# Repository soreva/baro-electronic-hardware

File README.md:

# README #

### What is this repository for? ###

This repository hosts the engineering designs for the Electronic Barometer designed by Soreva for use by SGS Weather and Environmental Systems.

### Who do I talk to? ###

Anirudh Ramesh, anirudh@soreva.co.in

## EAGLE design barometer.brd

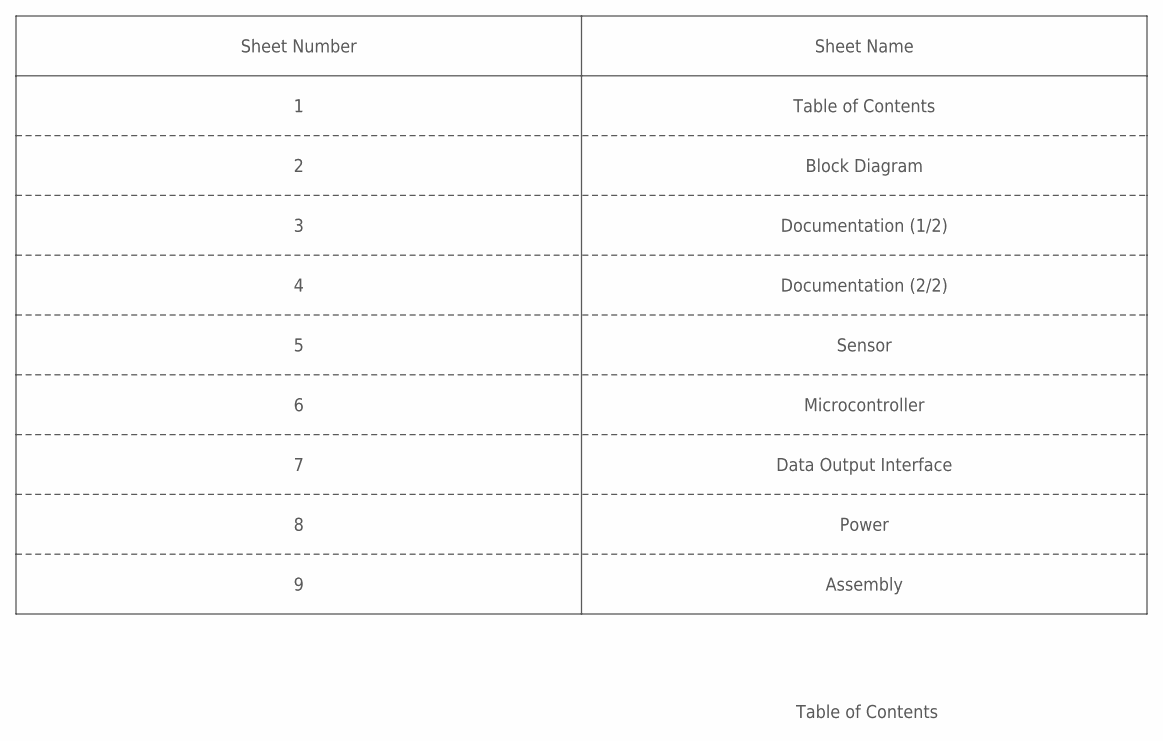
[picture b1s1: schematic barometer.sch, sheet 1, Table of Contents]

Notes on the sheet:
Table of Contents
Sheet Number
Sheet Name
Block Diagram
Documentation (1/2)
Documentation (2/2)
Sensor
Microcontroller
Data Output Interface
Power
Assembly

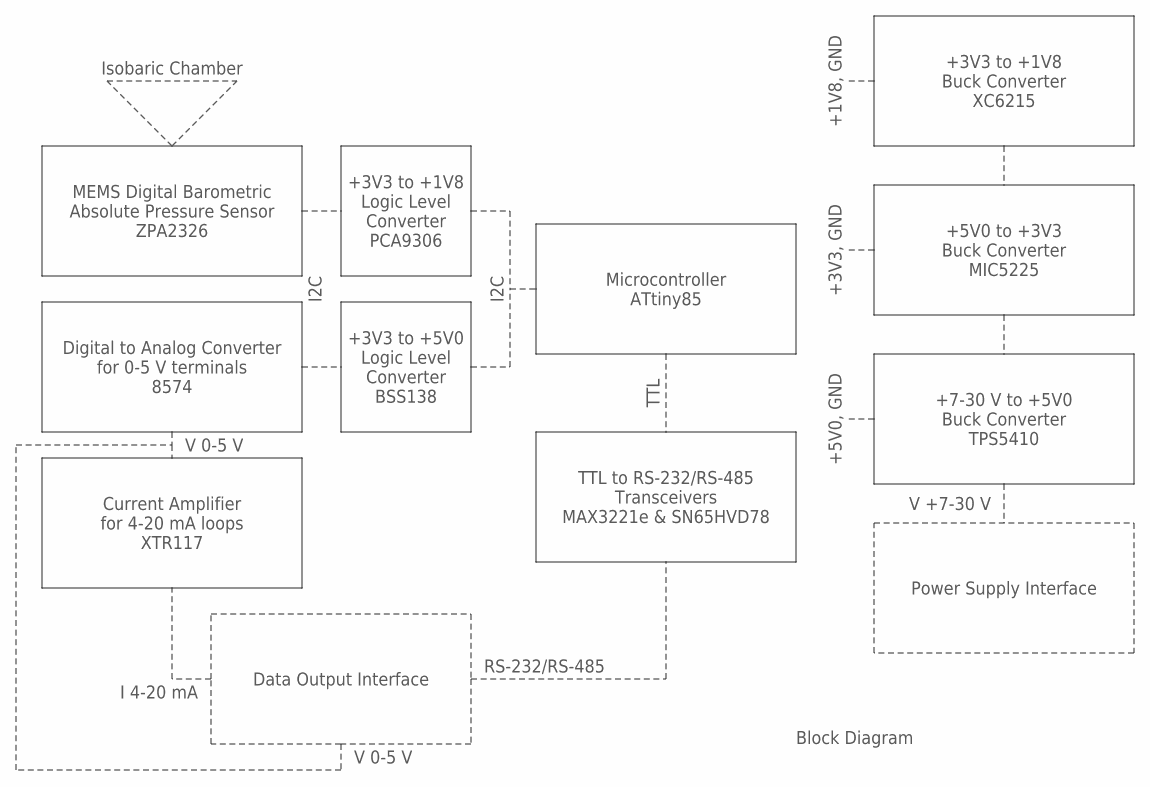
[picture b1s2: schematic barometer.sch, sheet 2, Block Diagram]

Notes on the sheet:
Block Diagram
MEMS Digital Barometric Absolute Pressure Sensor ZPA2326
Microcontroller ATtiny85
Digital to Analog Converter for 0-5 V terminals 8574
TTL to RS-232/RS-485 Transceivers MAX3221e & SN65HVD78
TTL
I2C
+3V3 to +1V8 Logic Level Converter PCA9306
+3V3 to +5V0 Logic Level Converter BSS138
Current Amplifier for 4-20 mA loops XTR117
Isobaric Chamber
Data Output Interface
Power Supply Interface
+7-30 V to +5V0 Buck Converter TPS5410
+5V0 to +3V3 Buck Converter MIC5225
+3V3 to +1V8 Buck Converter XC6215
V 0-5 V
I 4-20 mA
RS-232/RS-485
+5V0, GND
+3V3, GND
+1V8, GND
V +7-30 V

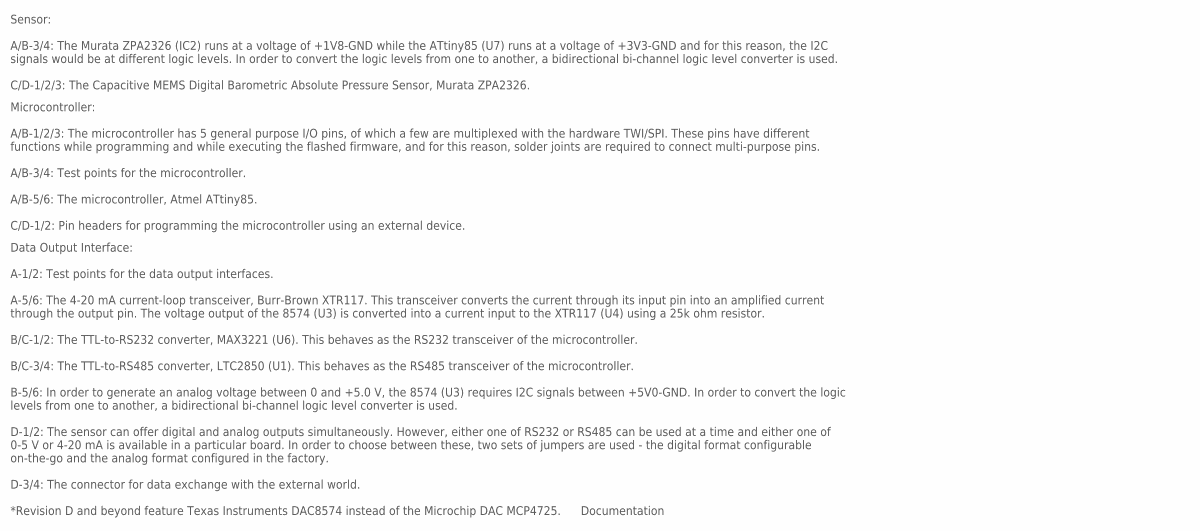
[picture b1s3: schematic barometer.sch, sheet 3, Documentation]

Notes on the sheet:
Documentation
Sensor: A/B-3/4: The Murata ZPA2326 (IC2) runs at a voltage of +1V8-GND while the ATtiny85 (U7) runs at a voltage of +3V3-GND and for this reason, the I2C signals would be at different logic levels. In order to convert the logic levels from one to another, a bidirectional bi-channel logic level con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
Microcontroller: A/B-1/2/3: The microcontroller has 5 general purpose I/O pins, of which a few are multiplexed with the hardware TWI/SPI. These pins have different functions while programming and while executing the flashed firmware, and for this reason, solder joints are required to connect multi-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
Data Output Interface: A-1/2: Test points for the data output interfaces. A-5/6: The 4-20 mA current-loop transceiver, Burr-Brown XTR117. This transceiver converts the current through its input pin into an amplified current through the output pin. The voltage output of the 8574 (U3) is converted in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

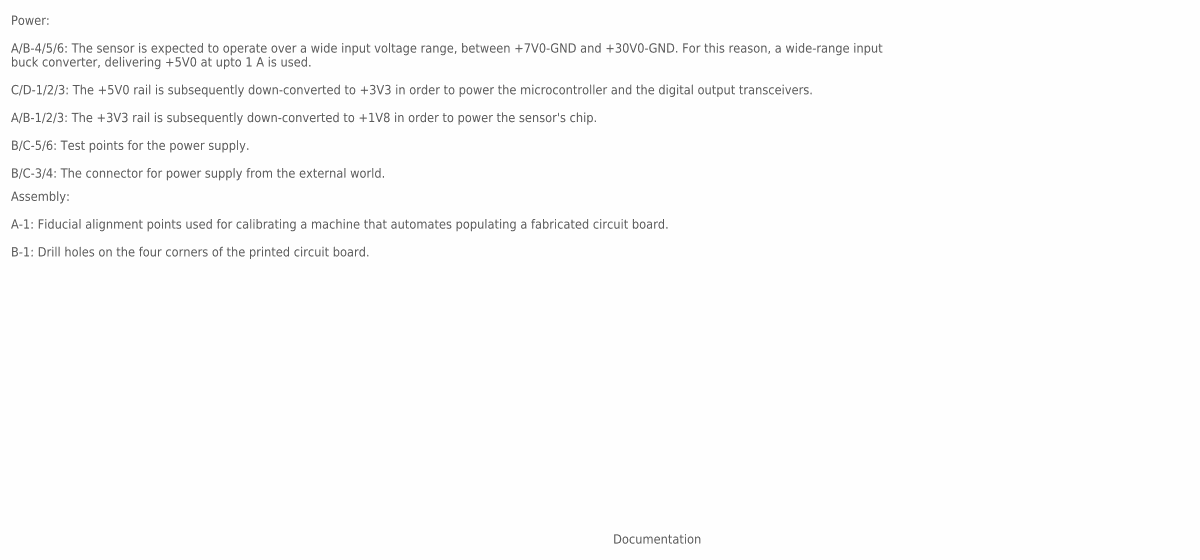
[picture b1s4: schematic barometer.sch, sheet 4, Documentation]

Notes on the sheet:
Documentation
Power: A/B-4/5/6: The sensor is expected to operate over a wide input voltage range, between +7V0-GND and +30V0-GND. For this reason, a wide-range input buck converter, delivering +5V0 at upto 1 A is used. C/D-1/2/3: The +5V0 rail is subsequently down-converted to +3V3 in order to power the microco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
Assembly: A-1: Fiducial alignment points used for calibrating a machine that automates populating a fabricated circuit board. B-1: Drill holes on the four corners of the printed circuit board.

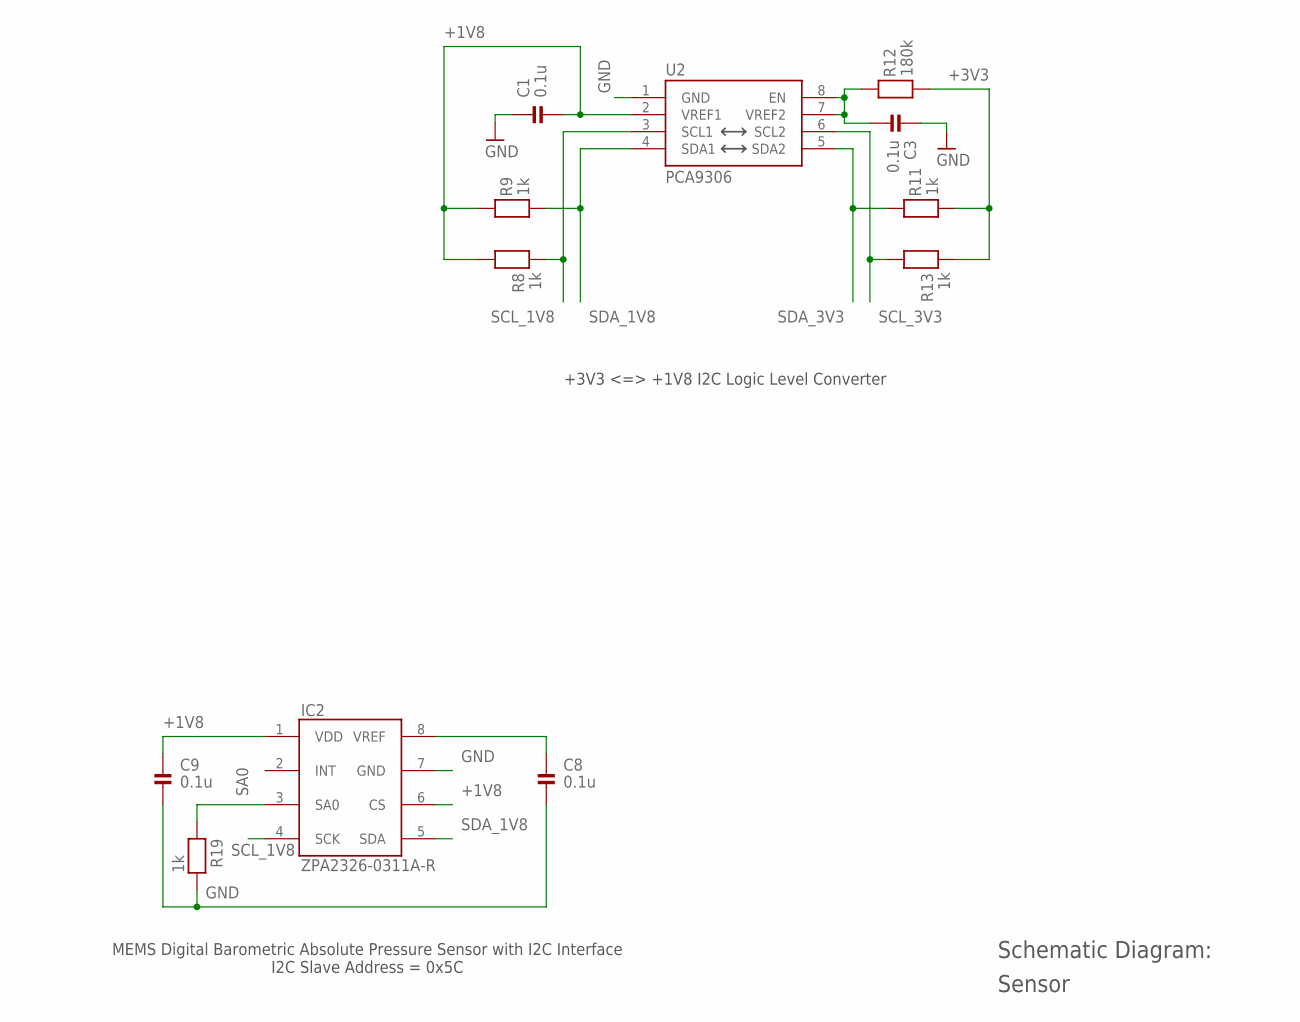
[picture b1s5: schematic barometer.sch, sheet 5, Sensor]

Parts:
C1, C3, C8, C9: 0.1u; 0603
IC2: ZPA2326-0311A-R; 2326
R8, R9, R11, R13, R19: 1k; 0603
R12: 180k; 0603
U2: PCA9306; PSOP-8

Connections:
+1V8: C1.2, C9.1, IC2.1 (VDD), IC2.6 (CS), R8.2, R9.2, U2.2 (VREF1); also elsewhere on the board
+3V3: R11.1, R12.1, R13.1; also elsewhere on the board
GND: C1.1, C3.1, C8.2, C9.2, IC2.7 (GND), R19.2, U2.1 (GND); also elsewhere on the board
SA0: IC2.3 (SA0), R19.1
SCL_1V8: IC2.4 (SCK), R8.1, U2.3 (SCL1)
SCL_3V3: R13.2, U2.6 (SCL2); also elsewhere on the board
SDA_1V8: IC2.5 (SDA), R9.1, U2.4 (SDA1)
SDA_3V3: R11.2, U2.5 (SDA2); also elsewhere on the board
VREF: C8.1, IC2.8 (VREF)
VREF_3V3: C3.2, R12.2, U2.7 (VREF2), U2.8 (EN)

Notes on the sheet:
Sensor
MEMS Digital Barometric Absolute Pressure Sensor with I2C Interface I2C Slave Address = 0x5C
+3V3 <=> +1V8 I2C Logic Level Converter
Schematic Diagram:

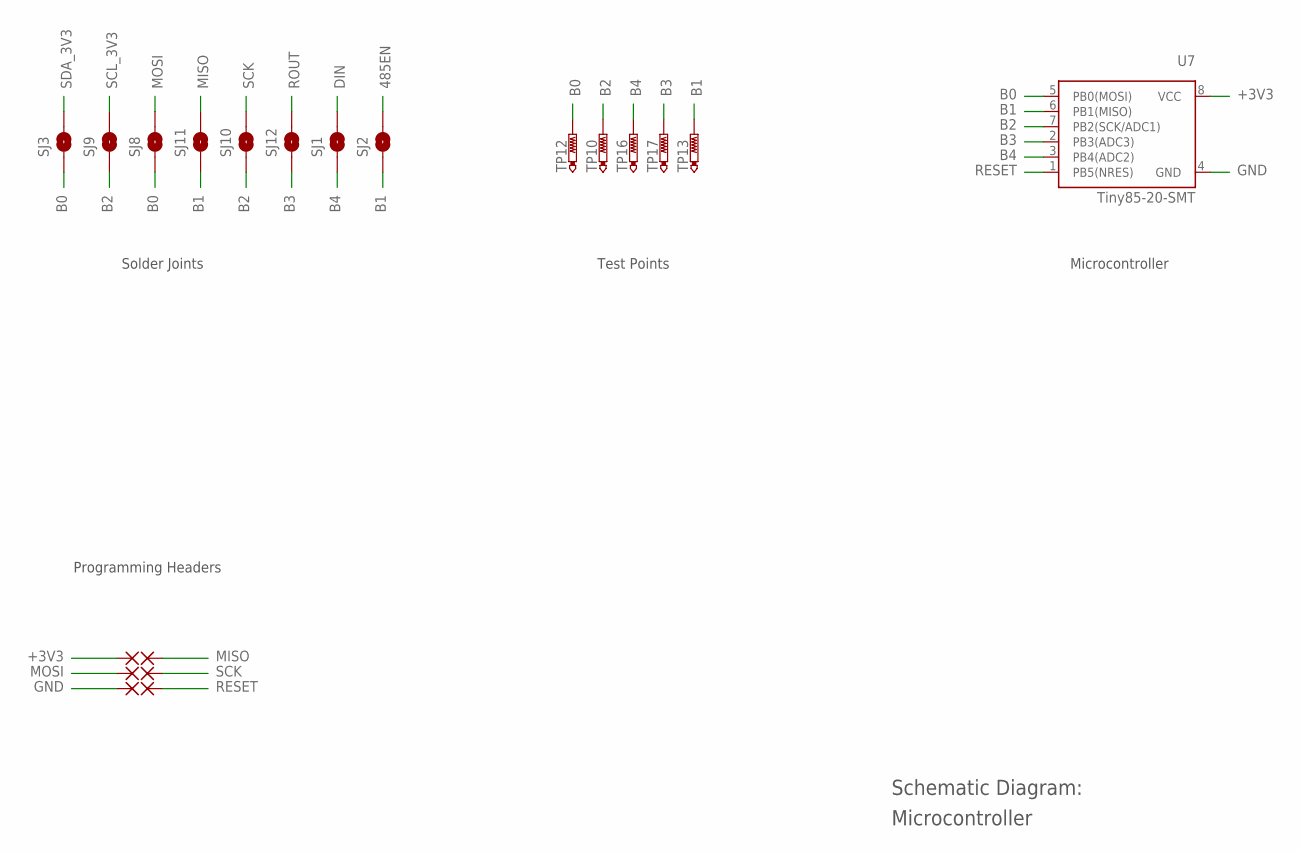
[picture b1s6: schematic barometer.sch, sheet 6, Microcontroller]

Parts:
PAD1, PAD2, PAD3, PAD4, PAD5, PAD6: SMD2; SMD1,27-2,54
SJ1, SJ2, SJ8, SJ9, SJ10, SJ11, SJ12: SOLDERJUMPERTRACE; SJ_2S-TRACE
SJ3: SOLDERJUMPERNO; SJ_2S-NO
TP10, TP12, TP13, TP16, TP17: PTR1B1,27; B1,27
U7: Tiny85-20-SMT; SO08-EIAJ_MCU

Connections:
485EN: SJ2.2; also elsewhere on the board
+3V3: PAD2.1, U7.8 (VCC); also elsewhere on the board
B0: SJ3.1, SJ8.1, TP12.TP, U7.5 (PB0(MOSI))
B1: SJ2.1, SJ11.1, TP13.TP, U7.6 (PB1(MISO))
B2: SJ9.1, SJ10.1, TP10.TP, U7.7 (PB2(SCK/ADC1))
B3: SJ12.1, TP17.TP, U7.2 (PB3(ADC3))
B4: SJ1.1, TP16.TP, U7.3 (PB4(ADC2))
DIN: SJ1.2; also elsewhere on the board
GND: PAD6.1, U7.4 (GND); also elsewhere on the board
MISO: PAD1.1, SJ11.2
MOSI: PAD4.1, SJ8.2
RESET: PAD5.1, U7.1 (PB5(NRES))
ROUT: SJ12.2; also elsewhere on the board
SCK: PAD3.1, SJ10.2
SCL_3V3: SJ9.2; also elsewhere on the board
SDA_3V3: SJ3.2; also elsewhere on the board

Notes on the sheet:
Microcontroller
Solder Joints
Test Points
Programming Headers
Schematic Diagram:

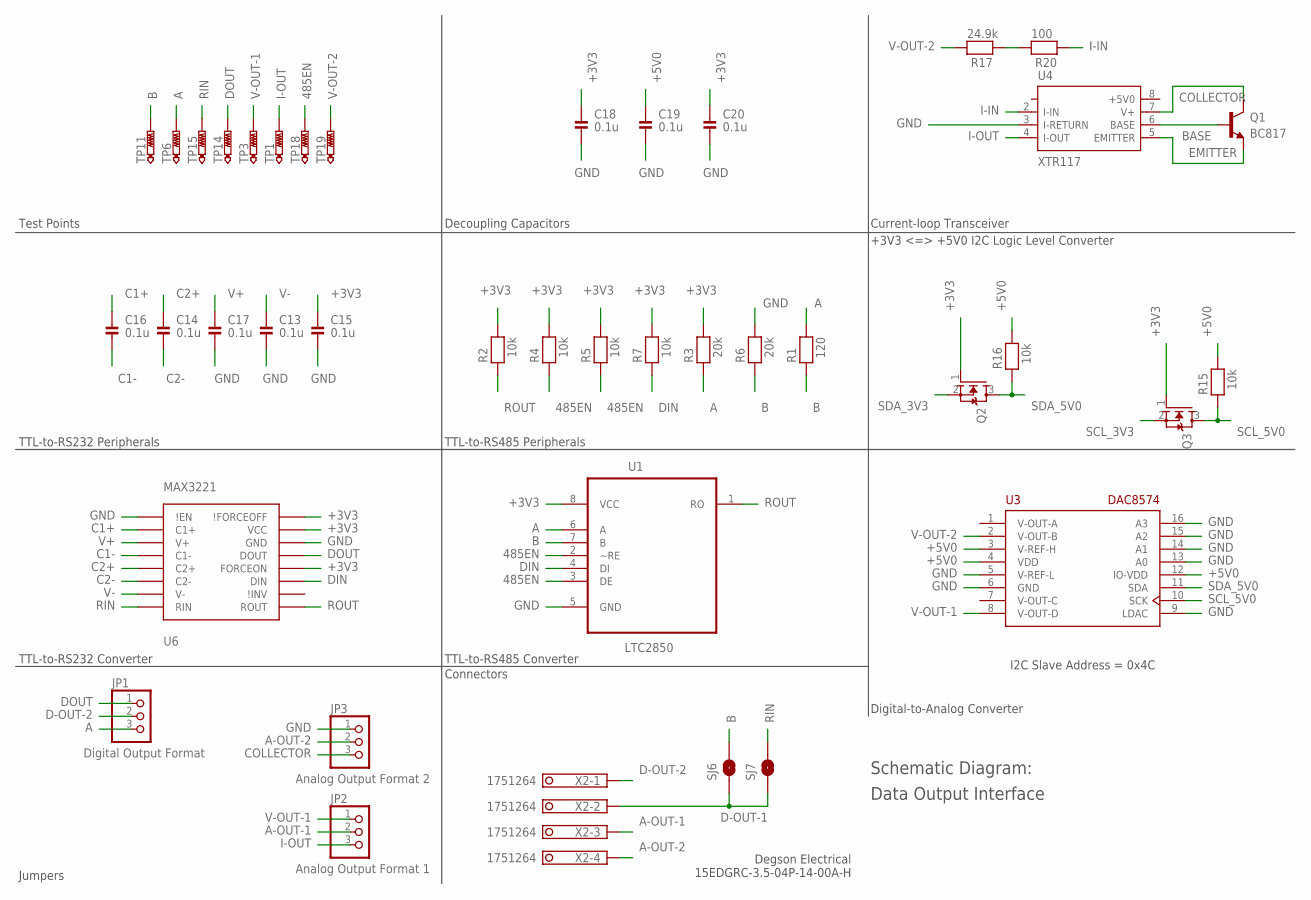
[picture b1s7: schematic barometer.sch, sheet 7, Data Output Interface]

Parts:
C13, C14, C15, C16, C17, C18, C19, C20: 0.1u; 0603
JP1: Digital Output Format; 1X03_SMT
JP2: Analog Output Format 1; 1X03_SMT
JP3: Analog Output Format 2; 1X03_SMT
Q1: BC817; SOT23-WIDE
Q2, Q3: MOSFET-NWIDE; SOT23-WIDE
R1: 120; 0603
R2, R4, R5, R7, R15, R16: 10k; 0603
R3, R6: 20k; 0603
R17: 24.9k; 0603
R20: 100; 0603
SJ6, SJ7: SOLDERJUMPERTRACE; SJ_2S-TRACE
TP1, TP3, TP6, TP11, TP14, TP15, TP18, TP19: PTR1B1,27; B1,27
U1: LTC2850; SOIC127P600X175-8N
U3: DAC8574; TSSOP16
U4: XTR117; MSOP8-0.65-3X3MM
U6: MAX3221; TSSOP16
X2: 1751264

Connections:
485EN: R4.1, R5.1, TP18.TP, U1.2 (~RE), U1.3 (DE); also elsewhere on the board
+3V3: C15.1, C18.1, C20.1, Q2.1 (G), Q3.1 (G), R2.2, R3.2, R4.2, R5.2, R7.2, U1.8 (VCC), U6.12 (FORCEON), U6.15 (VCC), U6.16 (\!FORCEOFF); also elsewhere on the board
+5V0: C19.1, R15.2, R16.2, U3.3 (V-REF-H), U3.4 (VDD), U3.12 (IO-VDD); also elsewhere on the board
A: JP1.3, R1.2, R3.1, TP6.TP, U1.6 (A)
A-OUT-1: JP2.2, X2.3
A-OUT-2: JP3.2, X2.4
B: R1.1, R6.1, SJ6.2, TP11.TP, U1.7 (B)
BASE: Q1.1 (B), U4.6 (BASE)
C1+: C16.1, U6.2 (C1+)
C1-: C16.2, U6.4 (C1-)
C2+: C14.1, U6.5 (C2+)
C2-: C14.2, U6.6 (C2-)
COLLECTOR: JP3.3, Q1.3 (C), U4.7 (V+)
D-OUT-1: SJ6.1, SJ7.1, X2.2
D-OUT-2: JP1.2, X2.1
DIN: R7.1, U1.4 (DI), U6.11 (DIN); also elsewhere on the board
DOUT: JP1.1, TP14.TP, U6.13 (DOUT)
EMITTER: Q1.2 (E), U4.5 (EMITTER)
GND: C13.2, C15.2, C17.2, C18.2, C19.2, C20.2, JP3.1, R6.2, U1.5 (GND), U3.5 (V-REF-L), U3.6 (GND), U3.9 (LDAC), U3.13 (A0), U3.14 (A1), U3.15 (A2), U3.16 (A3), U4.3 (I-RETURN), U6.1 (\!EN), U6.14 (GND); also elsewhere on the board
I-IN: R20.1, U4.2 (I-IN)
I-OUT: JP2.3, TP1.TP, U4.4 (I-OUT)
MEZZANINE-1: R17.1, R20.2
RIN: SJ7.2, TP15.TP, U6.8 (RIN)
ROUT: R2.1, U1.1 (RO), U6.9 (ROUT); also elsewhere on the board
SCL_3V3: Q3.2 (S); also elsewhere on the board
SCL_5V0: Q3.3 (D), R15.1, U3.10 (SCK)
SDA_3V3: Q2.2 (S); also elsewhere on the board
SDA_5V0: Q2.3 (D), R16.1, U3.11 (SDA)
V+: C17.1, U6.3 (V+)
V-: C13.1, U6.7 (V-)
V-OUT-1: JP2.1, TP3.TP, U3.8 (V-OUT-D)
V-OUT-2: R17.2, TP19.TP, U3.2 (V-OUT-B)

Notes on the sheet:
TTL-to-RS232 Converter
TTL-to-RS485 Converter
TTL-to-RS485 Peripherals
TTL-to-RS232 Peripherals
Data Output Interface
Jumpers
Test Points
Connectors
Digital-to-Analog Converter
Degson Electrical 15EDGRC-3.5-04P-14-00A-H
I2C Slave Address = 0x4C
+3V3 <=> +5V0 I2C Logic Level Converter
Current-loop Transceiver
Schematic Diagram:
Decoupling Capacitors

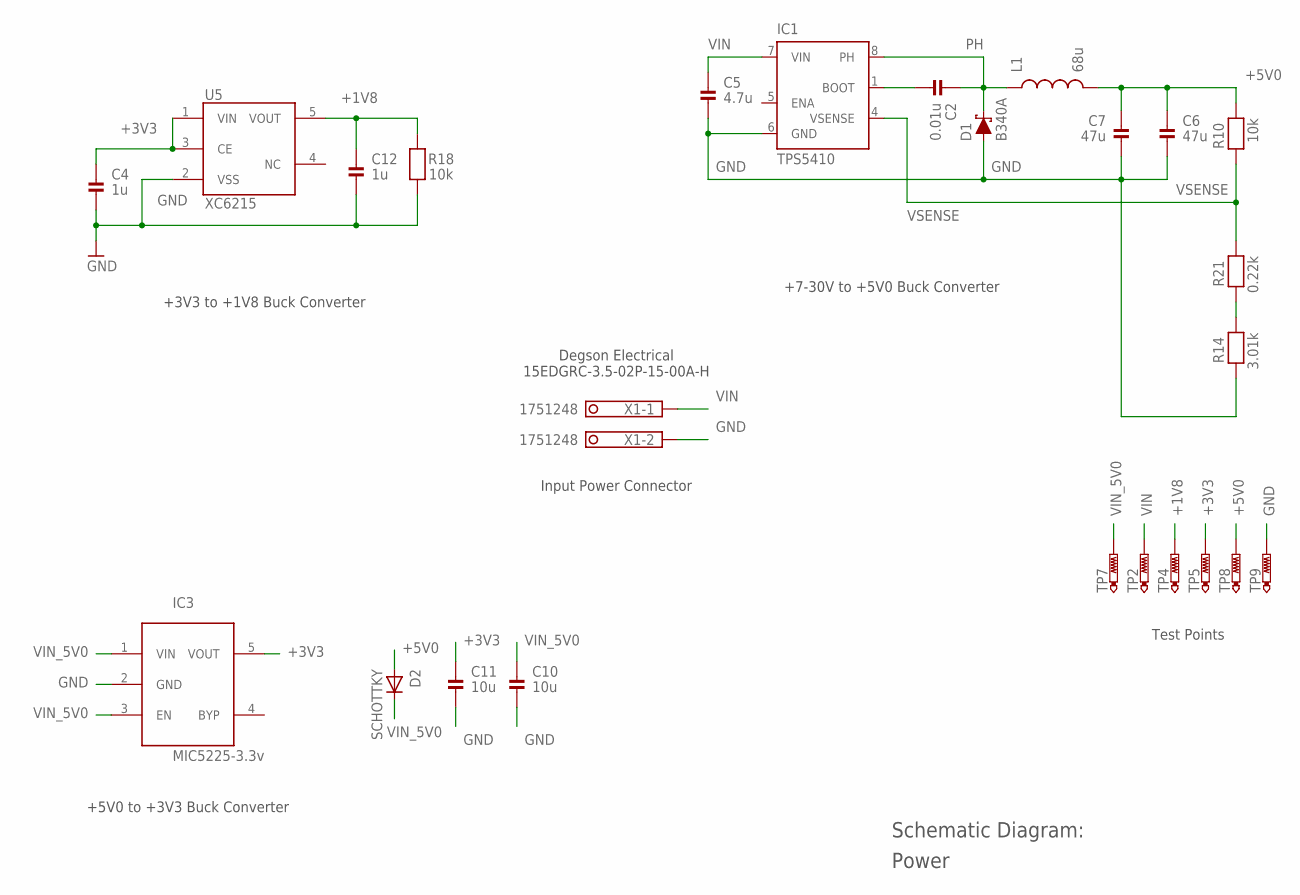
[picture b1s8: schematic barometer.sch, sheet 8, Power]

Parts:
C2: 0.01u; 0603
C4, C12: 1u; 0603
C5: 4.7u; 0805
C6, C7: 47u; 1206
C10, C11: 10u; 0603
D1: B340A; SMA-DIODE
D2: SCHOTTKY; SOD-123FL
IC1: TPS5410; D_R-PDSO-G08
IC3: MIC5225-3.3v; SOT23-5L
L1: 68u; VLS6045EX
R10, R18: 10k; 0603
R14: 3.01k; 0603
R21: 0.22k; 0603
TP2, TP4, TP5, TP7, TP8, TP9: PTR1B1,27; B1,27
U5: XC6215XC6215B182NR; SOT25
X1: 1751248

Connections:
+1V8: C12.1, R18.2, TP4.TP, U5.5 (VOUT); also elsewhere on the board
+3V3: C4.1, C11.1, IC3.5 (VOUT), TP5.TP, U5.1 (VIN), U5.3 (CE); also elsewhere on the board
+5V0: C6.1, C7.1, D2.A, L1.2, R10.2, TP8.TP; also elsewhere on the board
BOOT: C2.2, IC1.1 (BOOT)
GND: C4.2, C5.2, C6.2, C7.2, C10.2, C11.2, C12.2, D1.A, IC1.6 (GND), IC3.2 (GND), R14.1, R18.1, TP9.TP, U5.2 (VSS), X1.2; also elsewhere on the board
unnamed: R14.2, R21.1
PH: C2.1, D1.C, IC1.8 (PH), L1.1
VIN: C5.1, IC1.7 (VIN), TP2.TP, X1.1
VIN_5V0: C10.1, D2.C, IC3.1 (VIN), IC3.3 (EN), TP7.TP
VSENSE: IC1.4 (VSENSE), R10.1, R21.2

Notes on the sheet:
Power
Test Points
+3V3 to +1V8 Buck Converter
+7-30V to +5V0 Buck Converter
Input Power Connector
+5V0 to +3V3 Buck Converter
Degson Electrical 15EDGRC-3.5-02P-15-00A-H
Schematic Diagram:

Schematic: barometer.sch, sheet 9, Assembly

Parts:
FID1, FID2, FID3, FID4: FIDUCIAL1X2.5; FIDUCIAL-1X2.5
U$1, U$2, U$3, U$4: MOUNTINGHOLE2.75; MOUNTINGHOLE_2.75_PLATED

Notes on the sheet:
Assembly
Fiducial Alignment Points
Mounting Holes
Schematic Diagram:

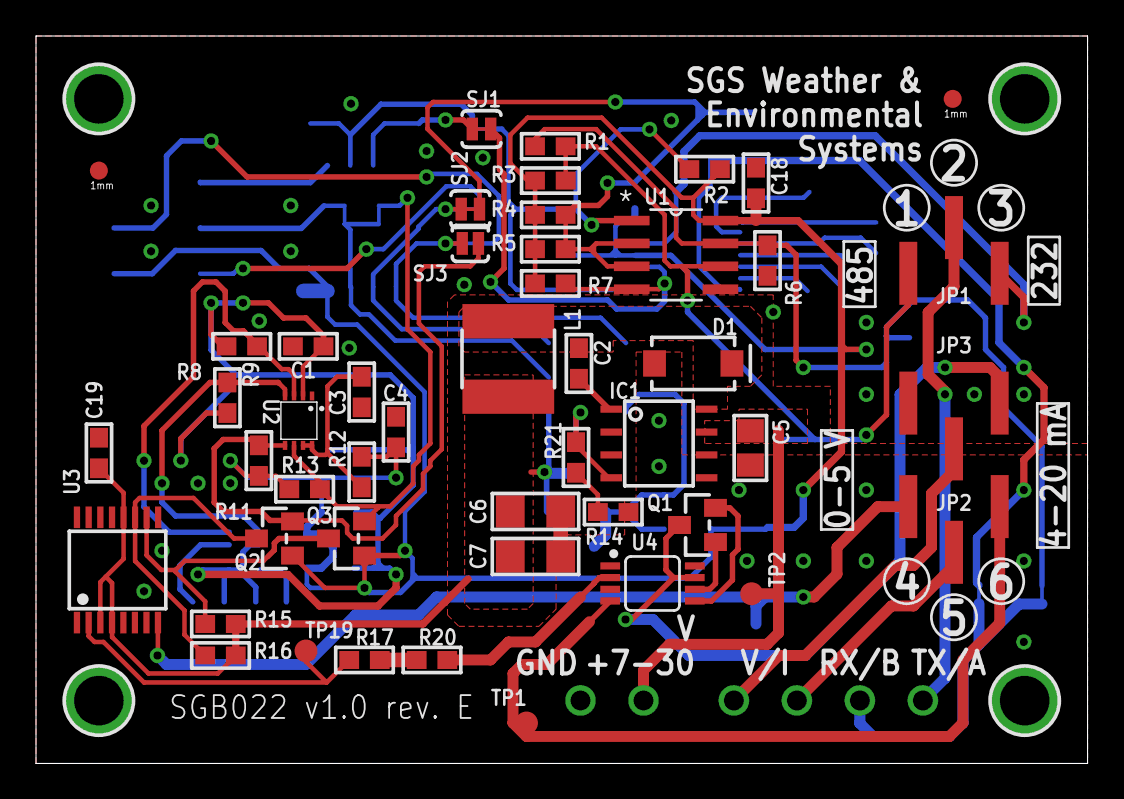
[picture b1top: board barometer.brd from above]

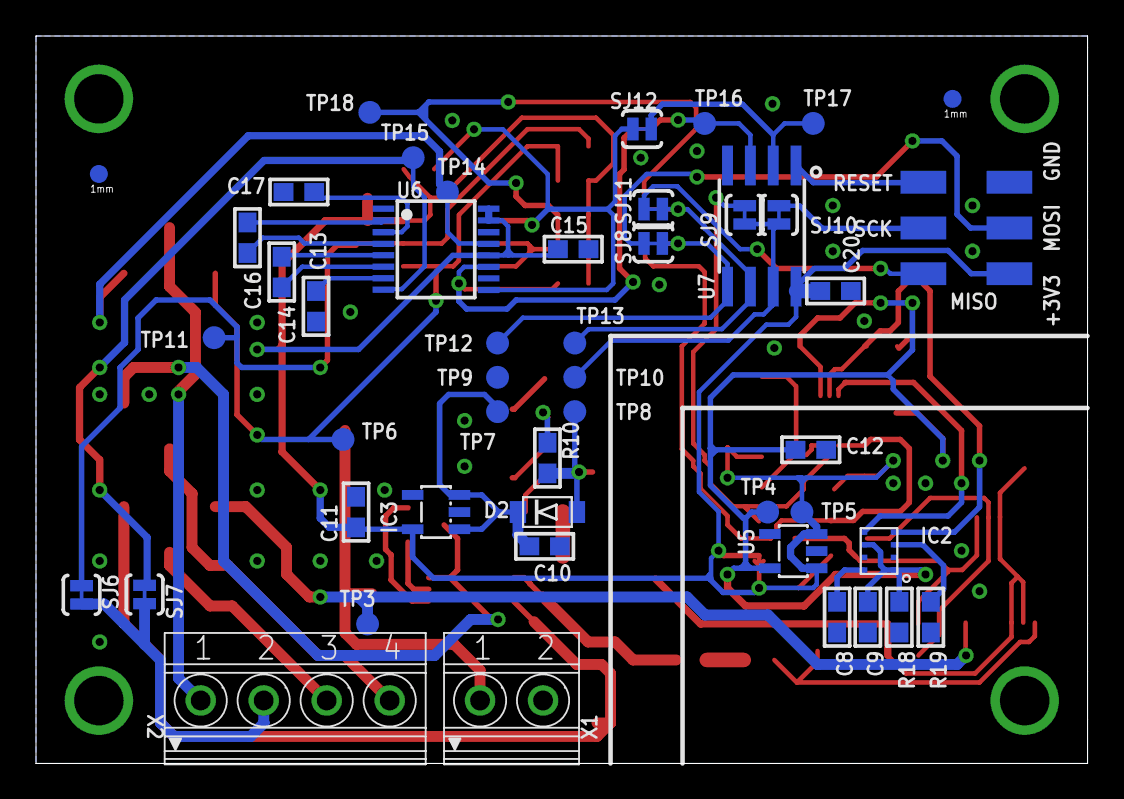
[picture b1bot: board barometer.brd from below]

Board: 2 copper layers, 58.4 x 40.4 mm, 105 parts (53 on the bottom side), 53 nets.

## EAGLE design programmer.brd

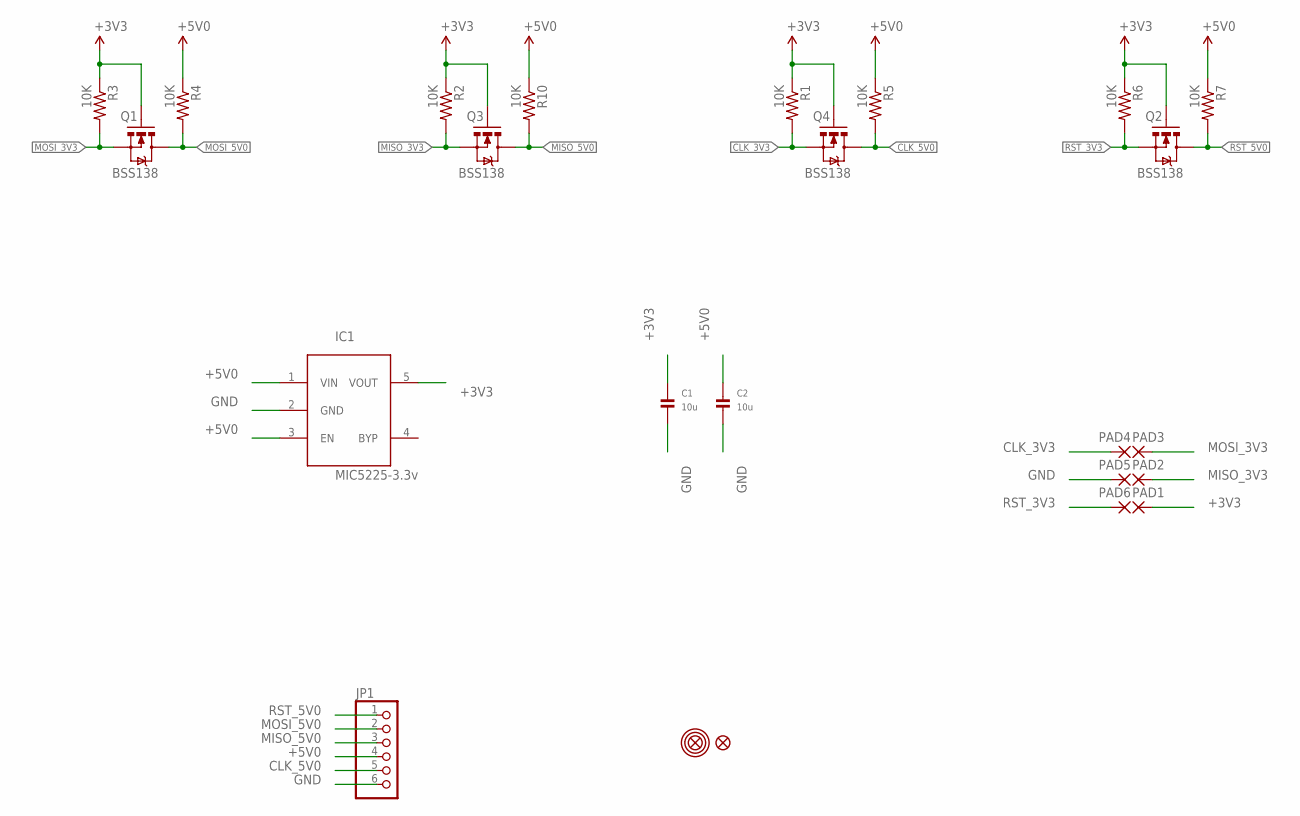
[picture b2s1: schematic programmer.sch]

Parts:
C1, C2: 10u; 0603
FID1, FID2: FIDUCIAL1X2.5; FIDUCIAL-1X2.5
IC1: MIC5225-3.3v; SOT23-5L
JP1: HEADER-1X6ROUND; 1X06_ROUND
PAD1, PAD2, PAD3, PAD4, PAD5, PAD6: WIREPADSMD1,27-254; SMD1,27-2,54
Q1, Q2, Q3, Q4: BSS138; SOT23-3
R1, R2, R3, R4, R5, R6, R7, R10: 10K; 0603-RES
U$1: MOUNTINGHOLE2.5; MOUNTINGHOLE_2.5_PLATED

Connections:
+3V3: C1.1, IC1.5 (VOUT), PAD1.1, Q1.1 (G), Q2.1 (G), Q3.1 (G), Q4.1 (G), R1.1, R2.1, R3.1, R6.1
+5V0: C2.1, IC1.1 (VIN), IC1.3 (EN), JP1.4, R4.1, R5.1, R7.1, R10.1
CLK_3V3: PAD4.1, Q4.2 (S), R1.2
CLK_5V0: JP1.5, Q4.3 (D), R5.2
GND: C1.2, C2.2, IC1.2 (GND), JP1.6, PAD5.1
MISO_3V3: PAD2.1, Q3.2 (S), R2.2
MISO_5V0: JP1.3, Q3.3 (D), R10.2
MOSI_3V3: PAD3.1, Q1.2 (S), R3.2
MOSI_5V0: JP1.2, Q1.3 (D), R4.2
RST_3V3: PAD6.1, Q2.2 (S), R6.2
RST_5V0: JP1.1, Q2.3 (D), R7.2

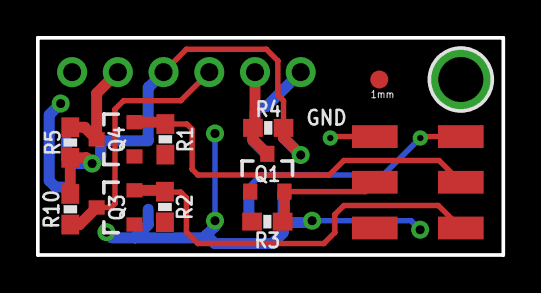
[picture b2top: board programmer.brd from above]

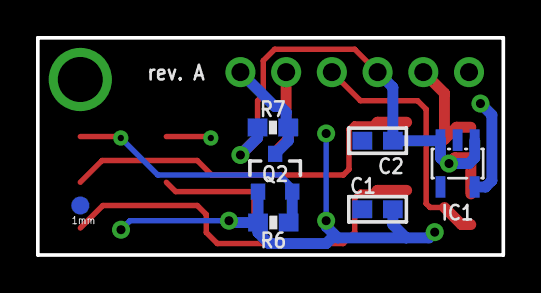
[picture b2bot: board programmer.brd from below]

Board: 2 copper layers, 25.9 x 12.1 mm, 25 parts (7 on the bottom side), 11 nets.

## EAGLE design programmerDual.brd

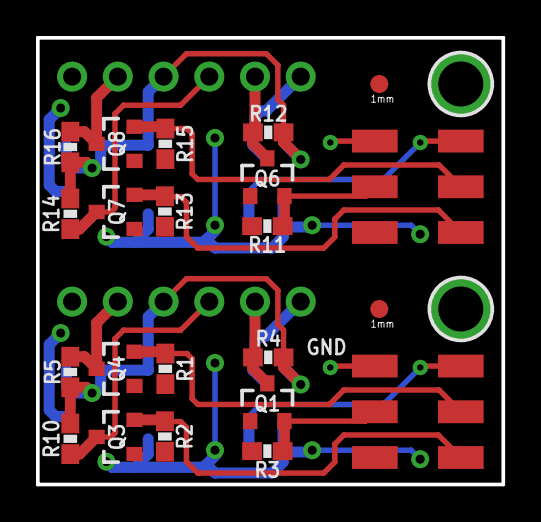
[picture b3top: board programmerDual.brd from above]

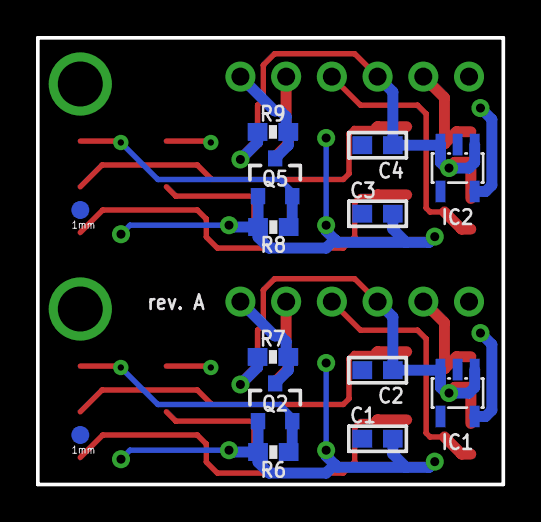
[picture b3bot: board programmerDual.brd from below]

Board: 2 copper layers, 25.9 x 24.8 mm, 50 parts (14 on the bottom side), 11 nets.

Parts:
C1, C2, C3, C4: 10u; 0603
FID1, FID2, FID3, FID4: FIDUCIAL1X2.5; FIDUCIAL-1X2.5
IC1, IC2: MIC5225-3.3v; SOT23-5L
JP1, JP2: 1X06_ROUND
PAD1, PAD2, PAD3, PAD4, PAD5, PAD6, PAD7, PAD8, PAD9, PAD10, PAD11, PAD12: WIREPADSMD1,27-254; SMD1,27-2,54
Q1, Q2, Q3, Q4, Q5, Q6, Q7, Q8: BSS138; SOT23-3
R1, R2, R3, R4, R5, R6, R7, R8, R9, R10, R11, R12, R13, R14, R15, R16: 10K; 0603-RES
U$1, U$2: MOUNTINGHOLE2.5; MOUNTINGHOLE_2.5_PLATED

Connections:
+3V3: C1.1, C3.1, IC1.5, IC2.5, PAD1.1, PAD7.1, Q1.1, Q2.1, Q3.1, Q4.1, Q5.1, Q6.1, Q7.1, Q8.1, R1.1, R2.1, R3.1, R6.1, R8.1, R11.1, R13.1, R15.1
+5V0: C2.1, C4.1, IC1.1, IC1.3, IC2.1, IC2.3, JP1.4, JP2.4, R4.1, R5.1, R7.1, R9.1, R10.1, R12.1, R14.1, R16.1
CLK_3V3: PAD4.1, PAD10.1, Q4.2, Q8.2, R1.2, R15.2
CLK_5V0: JP1.5, JP2.5, Q4.3, Q8.3, R5.2, R16.2
GND: C1.2, C2.2, C3.2, C4.2, IC1.2, IC2.2, JP1.6, JP2.6, PAD5.1, PAD11.1
MISO_3V3: PAD2.1, PAD8.1, Q3.2, Q7.2, R2.2, R13.2
MISO_5V0: JP1.3, JP2.3, Q3.3, Q7.3, R10.2, R14.2
MOSI_3V3: PAD3.1, PAD9.1, Q1.2, Q6.2, R3.2, R11.2
MOSI_5V0: JP1.2, JP2.2, Q1.3, Q6.3, R4.2, R12.2
RST_3V3: PAD6.1, PAD12.1, Q2.2, Q5.2, R6.2, R8.2
RST_5V0: JP1.1, JP2.1, Q2.3, Q5.3, R7.2, R9.2

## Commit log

2018-04-03 Add electronic barometer's initial prototype's schematic and board layout
2018-04-03 Add manufacturer part number for terminal block connectors
2018-04-03 Add compatibility note inserted by EAGLE
2018-04-03 Add .gitignore
2018-04-04 Fix connector-connector-pinhole-board clearance
2018-04-04 Draw boundaries for pressure sensing chamber
2018-04-04 Shift sensor to bottom layer
2018-04-04 Rearrange components inside the pressure receptacle
2018-04-04 Rearrange component names on both layers
2018-04-04 Remove jumper indicators
2018-04-04 Replace surface-mount jumper with through-hole SPDT sliding switch
2018-04-04 Fix incorrect connections from/to MAX3221 and PCA9306
2018-04-04 Remove unused signal and net
2018-04-04 Rearrange vias
2018-04-04 Connect microcontroller to RS-232 and RS-485 transceivers
2018-04-04 Connect analog output pins to test points
2018-04-06 Rename self-created libraries
2018-04-06 Add self-created libraries
2018-04-06 Add package.json
2018-04-06 Substitute through-hole SPDT sliding switch
2018-04-06 Indicate switch connections using silkscreen text
2018-04-06 Rename switches
2018-04-06 Indicate programming pin connections using silkscreen text
2018-04-06 Indicate power and communication pin connections using silkscreen text
2018-04-06 Move boundaries of pressure sensing chamber to "Bottom Documentation" layer
2018-04-06 Fix incorrect formatting of testpoints' labels
2018-04-06 Fix intrusion of schottky diode in the pressure sensing chamber
2018-04-06 Enable top and bottom documentation layers
2018-04-06 Fix connector-drill clearance
2018-04-06 Label dimensions and clearances
2018-04-06 Edit .gitignore
2018-04-06 Rotate switch that picks analog output format
2018-04-07 Add Gerber and Excellon files' extensions to .gitignore
2018-04-07 Add CAM processor job file containing frequently used configuration
2018-04-07 Fix overlapping text by moving connector label
2018-04-07 Move logo and part number label
2018-04-09 Move sliding switch's handle's footprint's layer
2018-04-17 Change form factor of 47uF capacitors from 0603 to 1206
2018-04-18 Clear area around mounting holes
2018-04-18 Realign connector label text
2018-04-18 Truncate length between terminal block connectors
2018-04-18 Fix PCB name
2018-04-18 Remove logo
2018-04-18 Add company name
2018-04-18 Add compatibility note
2018-04-18 Sweep vias off exclusion zone
2018-04-18 Mark approximate boundaries of exclusion zone on bottom silkscreen
2018-04-18 Reformat programming jumper's label's text
2018-04-19 Fix overlapping features at the bottom layer's silkscreen
2018-04-19 Displace test point from exclusion zone's periphery
2018-04-25 Add test point for 485 transmit/receive function control
2018-04-25 Integrate 485 transmit/receive function control with the microcontroller
2018-04-25 Beautify vias and silkscreen text
2018-04-25 Add orientation dot for ZPA2326
2018-04-25 Add silkscreen label for PCA9306
2018-04-26 Add design files for the AVR programmer interface board
2018-04-27 Fix interchanged I and V out silkscreen labels
2018-05-08 Add clearance between terminal block connectors
2018-05-09 Indicate clearance between terminal block connectors
2018-05-09 Fix overlapping text in the schematic
2018-05-09 Replace through-hole SPDT sliding switch with surface-mount jumper
2018-05-09 Replace through-hole with surface-mount for programming headers
2018-05-09 Fix semantics and formatting
2018-05-09 Increase PCB width by 2.0mm
2018-05-09 Move top-right fiducial alignment point
2018-05-12 Move distance measurement label to correct layer
2018-05-12 Move silkscreen text to correct/appropriate layer, position and orientation
2018-05-15 Extend drills by 2.0mm
2018-05-29 Migrate to EAGLE v9.0.0
2018-05-29 Fix wide-range input buck converter
2018-05-29 Add custom library for voltage level shifters
2018-05-29 Fork library containing retired SparkFun elements
2018-05-29 Expand layers on schematic and board layout
2018-05-29 Migrate to customised/forked libraries
2018-05-29 Update all libraries
2018-05-29 Add third-party libraries
2018-05-29 Fix inductor's footprint's dimensions
2018-05-29 Fix DAC output's voltage reference from +3V3 to +5V0
2018-05-29 Indicate the I2C slave address corresponding to the evaluated DAC
2018-05-29 Add EAGLE v9.0.0 note
2018-05-29 Add 0-5 V to 4-20 mA converter
2018-05-29 Annotate portions of "Data Output Interface" sheet of the schematic
2018-05-29 Improve legibility on top silkscreen text layer
2018-05-29 Add library containing current-loop transceiver footprint
2018-05-30 Smash mounting-holes
2018-05-30 Edit silkscreen text size
2018-05-30 Implement sequential numbering for all component names
2018-05-30 Change typeface from proportional to vector wherever applicable
2018-05-30 Displace fiducial alignment points
2018-05-30 Edit CAM processor job file containing frequently used configuration
2018-05-30 Add fiducial alignment points on the bottom copper layer
2018-05-30 Rename frame in microbuilder.eu library
2018-05-30 Rename diode in wide-range input buck converter
2018-05-30 Smash all schematic parts and beautify their attributes
2018-06-02 Fix acute and right angles
2018-06-02 Migrate to EAGLE v9.0.1
2018-06-02 Fix formatting in schematic
2018-06-02 Rename organization
2018-06-02 Add documentation sheets
2018-06-02 Edit description of the sensor's chip
2018-06-02 Migrate microbuilder library to EAGLE v9.0.1
2018-06-02 Add frame for SGS Weather and Environmental Systems
2018-06-02 Migrate to custom frame
2018-06-02 Improve legibility in the schematic
2018-06-08 Edit A4 frame
2018-06-08 Add "Block Diagram" sheet
2018-06-08 Edit "Documentation" sheet
2018-06-08 Fix airwires
2018-06-08 Split XTR117 input resistance into two series resistors
2018-06-11 Use 0805 ceramic capacitor to reduce component cost
2018-06-11 Add table of contents
2018-06-15 Shrink via drills to 0.45mm in order to enable filling
2018-07-18 Erase isobaric chamber's boundaries
2018-07-24 Edit dimension labels and text properties
2018-07-24 Accommodate inverted connector assembly
2018-07-24 Clean up routing
2018-07-24 Shift testpad label away from restricted area
2018-07-26 Fix clearance between terminal block connectors
2018-07-26 Edit pin header and jumper labels
2018-07-26 Apply cosmetic changes on revision B release
2018-07-30 Fix spelling mistake in barometer documentation
2018-07-30 Update ATtiny programming interface board
2018-08-17 Move terminal block connector's silkscreen features to the opposite layer
2018-08-17 Migrate to EAGLE v9.1.2
2018-08-17 Edit frame in programmer's schematic
2018-08-17 Add new frame in microbuilder.lbr
2018-08-17 Duplicate programmer board to create panel of two
2018-08-17 Move overlapping text
2018-08-27 Migrate microbuilder library to EAGLE v9.1.2
2018-08-27 Edit grid properties of microbuilder.eu library
2018-08-27 Add 2.75 mm diameter mounting hole
2018-08-27 Include 2.75 mm diameter mounting hole
2018-08-27 Update mounting holes in schematic and layout
2018-08-27 Fix mounting hole dimension labels in layout
2018-08-27 Migrate schematic to EAGLE v9.1.2
2018-08-31 Fix +5V0 buck converter's feedback circuit
2018-09-04 Separate analog output formats
2018-09-04 Edit documentation
2018-09-04 Reroute signals at the vicinity of the analog output format selection area
2018-09-04 Move GND plane stitching vias to align with other vias
2018-09-04 Remove wire stubs
2018-09-24 Fix RS-485 malfunction
2018-11-05 Fix +5V0 buck converter output
2018-11-24 Add DAC8574 to Texas Instruments library
2018-11-24 Migrate to EAGLE v9.2.2
2018-11-24 Add decoupling capacitors for all integrated circuits
2018-11-24 Add attributes for frames in the sheets of the schematic
2018-11-24 Realign text
2018-11-24 Change pin configuration of the digital data output's terminal block connector
2018-11-24 Migrate to revision D
2018-11-24 Replace Microchip DAC 4725 with TI DAC 8574
2018-11-24 Implement all placement and routing updates for revision D
2018-11-24 Improve silkscreen text placement
2018-11-24 Optimize via placement and routing
2018-11-28 Fix feedback resistance in +5V0 buck converter
2018-11-28 Add test point for DAC output corresponding to 4-20 mA current loop
2018-11-28 Fix schematic documentation
2018-12-29 Add additional jumper for analog output format
2018-12-29 Remove trace in solder jumper SJ3
2018-12-29 Migrate to revision E
2019-01-10 Move silkscreen text indicating analog output format selection jumper positions
2019-07-11 Create LICENSE
2019-08-23 Add missing names of manufacturers of transceivers in the schematic
2019-08-23 Add missing info on DAC8574

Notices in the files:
parts and their libraries:
microbuilder: This work is placed in the public domain, and may be freely used for commercial and non-commercial work with the following conditions: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
SparkFun-DiscreteSemi: Licensing: Creative Commons ShareAlike 4.0 International - https://creativecommons.org/licenses/by-sa/4.0
